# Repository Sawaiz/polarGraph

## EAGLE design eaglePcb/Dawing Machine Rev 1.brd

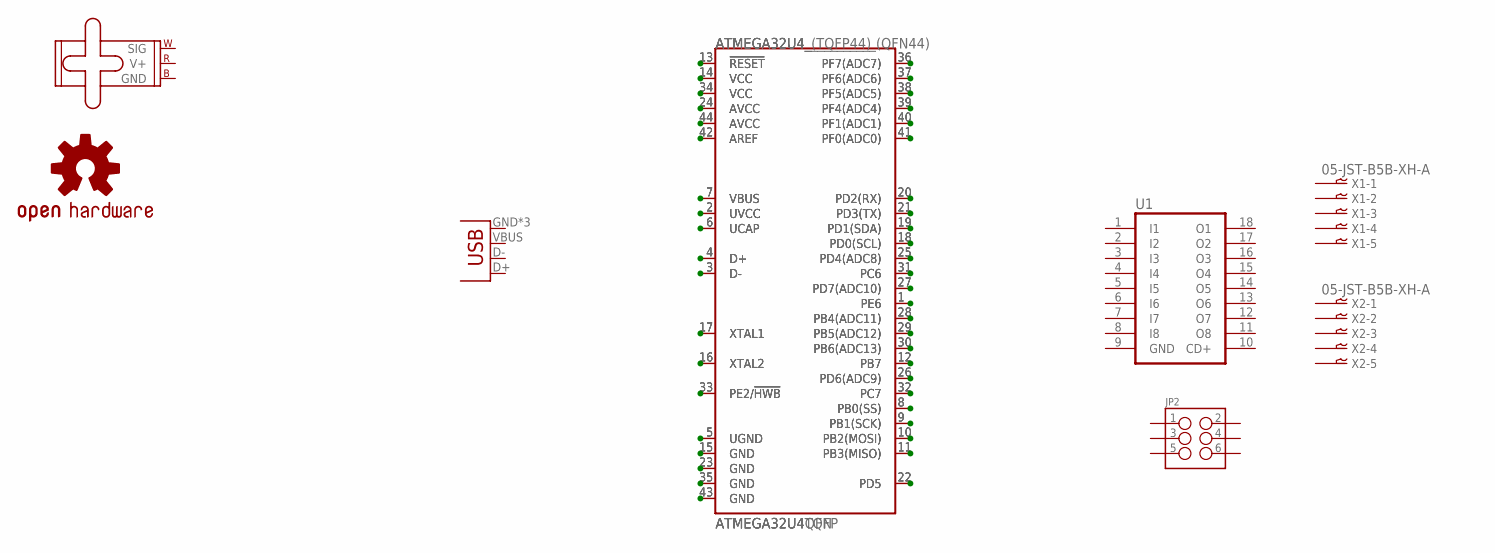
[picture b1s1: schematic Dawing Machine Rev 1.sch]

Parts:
ATMEGA32U4_(TQFP44): ATMEGA32U4TQFP; SPARKFUN-DIGITALIC_TQFP44
ATMEGA32U4___________(QFN44): ATMEGA32U4QFN; SPARKFUN-DIGITALIC_QFN-44
JP1: USB-MICROB
JP2: M03X2SMT; 2X3_SMT_POSTS
LOGO1: OSHW-LOGOS; OSHW-LOGO-S
M1: SMALL_SERVO; 1X03
U1: ULN2803AFW; SO18W
X1, X2: 05-JST-B5B-XH-A; B5B-XH

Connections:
GND: U1.9 (GND)
unnamed: ATMEGA32U4_(TQFP44).13 (!RESET), ATMEGA32U4___________(QFN44).13 (!RESET)
unnamed: ATMEGA32U4_(TQFP44).42 (AREF), ATMEGA32U4___________(QFN44).42 (AREF)
unnamed: ATMEGA32U4_(TQFP44).24 (AVCC), ATMEGA32U4___________(QFN44).24 (AVCC)
unnamed: ATMEGA32U4_(TQFP44).44 (AVCC), ATMEGA32U4___________(QFN44).44 (AVCC)
unnamed: ATMEGA32U4_(TQFP44).4 (D+), ATMEGA32U4___________(QFN44).4 (D+)
unnamed: ATMEGA32U4_(TQFP44).3 (D-), ATMEGA32U4___________(QFN44).3 (D-)
unnamed: ATMEGA32U4_(TQFP44).15 (GND), ATMEGA32U4___________(QFN44).15 (GND)
unnamed: ATMEGA32U4_(TQFP44).23 (GND), ATMEGA32U4___________(QFN44).23 (GND)
unnamed: ATMEGA32U4_(TQFP44).35 (GND), ATMEGA32U4___________(QFN44).35 (GND)
unnamed: ATMEGA32U4_(TQFP44).43 (GND), ATMEGA32U4___________(QFN44).43 (GND)
unnamed: ATMEGA32U4_(TQFP44).8 (PB0(SS)), ATMEGA32U4___________(QFN44).8 (PB0(SS))
unnamed: ATMEGA32U4_(TQFP44).9 (PB1(SCK)), ATMEGA32U4___________(QFN44).9 (PB1(SCK))
unnamed: ATMEGA32U4_(TQFP44).10 (PB2(MOSI)), ATMEGA32U4___________(QFN44).10 (PB2(MOSI))
unnamed: ATMEGA32U4_(TQFP44).11 (PB3(MISO)), ATMEGA32U4___________(QFN44).11 (PB3(MISO))
unnamed: ATMEGA32U4_(TQFP44).28 (PB4(ADC11)), ATMEGA32U4___________(QFN44).28 (PB4(ADC11))
unnamed: ATMEGA32U4_(TQFP44).29 (PB5(ADC12)), ATMEGA32U4___________(QFN44).29 (PB5(ADC12))
unnamed: ATMEGA32U4_(TQFP44).30 (PB6(ADC13)), ATMEGA32U4___________(QFN44).30 (PB6(ADC13))
unnamed: ATMEGA32U4_(TQFP44).12 (PB7), ATMEGA32U4___________(QFN44).12 (PB7)
unnamed: ATMEGA32U4_(TQFP44).31 (PC6), ATMEGA32U4___________(QFN44).31 (PC6)
unnamed: ATMEGA32U4_(TQFP44).32 (PC7), ATMEGA32U4___________(QFN44).32 (PC7)
unnamed: ATMEGA32U4_(TQFP44).18 (PD0(SCL)), ATMEGA32U4___________(QFN44).18 (PD0(SCL))
unnamed: ATMEGA32U4_(TQFP44).19 (PD1(SDA)), ATMEGA32U4___________(QFN44).19 (PD1(SDA))
unnamed: ATMEGA32U4_(TQFP44).20 (PD2(RX)), ATMEGA32U4___________(QFN44).20 (PD2(RX))
unnamed: ATMEGA32U4_(TQFP44).21 (PD3(TX)), ATMEGA32U4___________(QFN44).21 (PD3(TX))
unnamed: ATMEGA32U4_(TQFP44).25 (PD4(ADC8)), ATMEGA32U4___________(QFN44).25 (PD4(ADC8))
unnamed: ATMEGA32U4_(TQFP44).22 (PD5), ATMEGA32U4___________(QFN44).22 (PD5)
unnamed: ATMEGA32U4_(TQFP44).26 (PD6(ADC9)), ATMEGA32U4___________(QFN44).26 (PD6(ADC9))
unnamed: ATMEGA32U4_(TQFP44).27 (PD7(ADC10)), ATMEGA32U4___________(QFN44).27 (PD7(ADC10))
unnamed: ATMEGA32U4_(TQFP44).33 (PE2/!HWB), ATMEGA32U4___________(QFN44).33 (PE2/!HWB)
unnamed: ATMEGA32U4_(TQFP44).1 (PE6), ATMEGA32U4___________(QFN44).1 (PE6)
unnamed: ATMEGA32U4_(TQFP44).41 (PF0(ADC0)), ATMEGA32U4___________(QFN44).41 (PF0(ADC0))
unnamed: ATMEGA32U4_(TQFP44).40 (PF1(ADC1)), ATMEGA32U4___________(QFN44).40 (PF1(ADC1))
unnamed: ATMEGA32U4_(TQFP44).39 (PF4(ADC4)), ATMEGA32U4___________(QFN44).39 (PF4(ADC4))
unnamed: ATMEGA32U4_(TQFP44).38 (PF5(ADC5)), ATMEGA32U4___________(QFN44).38 (PF5(ADC5))
unnamed: ATMEGA32U4_(TQFP44).37 (PF6(ADC6)), ATMEGA32U4___________(QFN44).37 (PF6(ADC6))
unnamed: ATMEGA32U4_(TQFP44).36 (PF7(ADC7)), ATMEGA32U4___________(QFN44).36 (PF7(ADC7))
unnamed: ATMEGA32U4_(TQFP44).6 (UCAP), ATMEGA32U4___________(QFN44).6 (UCAP)
unnamed: ATMEGA32U4_(TQFP44).5 (UGND), ATMEGA32U4___________(QFN44).5 (UGND)
unnamed: ATMEGA32U4_(TQFP44).2 (UVCC), ATMEGA32U4___________(QFN44).2 (UVCC)
unnamed: ATMEGA32U4_(TQFP44).7 (VBUS), ATMEGA32U4___________(QFN44).7 (VBUS)
unnamed: ATMEGA32U4_(TQFP44).14 (VCC), ATMEGA32U4___________(QFN44).14 (VCC)
unnamed: ATMEGA32U4_(TQFP44).34 (VCC), ATMEGA32U4___________(QFN44).34 (VCC)
unnamed: ATMEGA32U4_(TQFP44).17 (XTAL1), ATMEGA32U4___________(QFN44).17 (XTAL1)
unnamed: ATMEGA32U4_(TQFP44).16 (XTAL2), ATMEGA32U4___________(QFN44).16 (XTAL2)

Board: 2 copper layers, 9 parts (0 on the bottom side), 44 nets, no tracks yet.

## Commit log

2015-11-26 full clean

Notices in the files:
parts and their libraries:
SparkFun-DigitalIC: Licensing: CC v3.0 Share-Alike You are welcome to use this library for commercial purposes.
